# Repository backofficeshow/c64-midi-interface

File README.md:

# c64-midi-interface

A hardware layout to accompany this website what I found while in a stream:

http://little-scale.blogspot.com/2010/03/how-to-make-commodore-64-midi-interface.html

Do please check before having 200 boards made up.

Bye!

xxxx Dr A

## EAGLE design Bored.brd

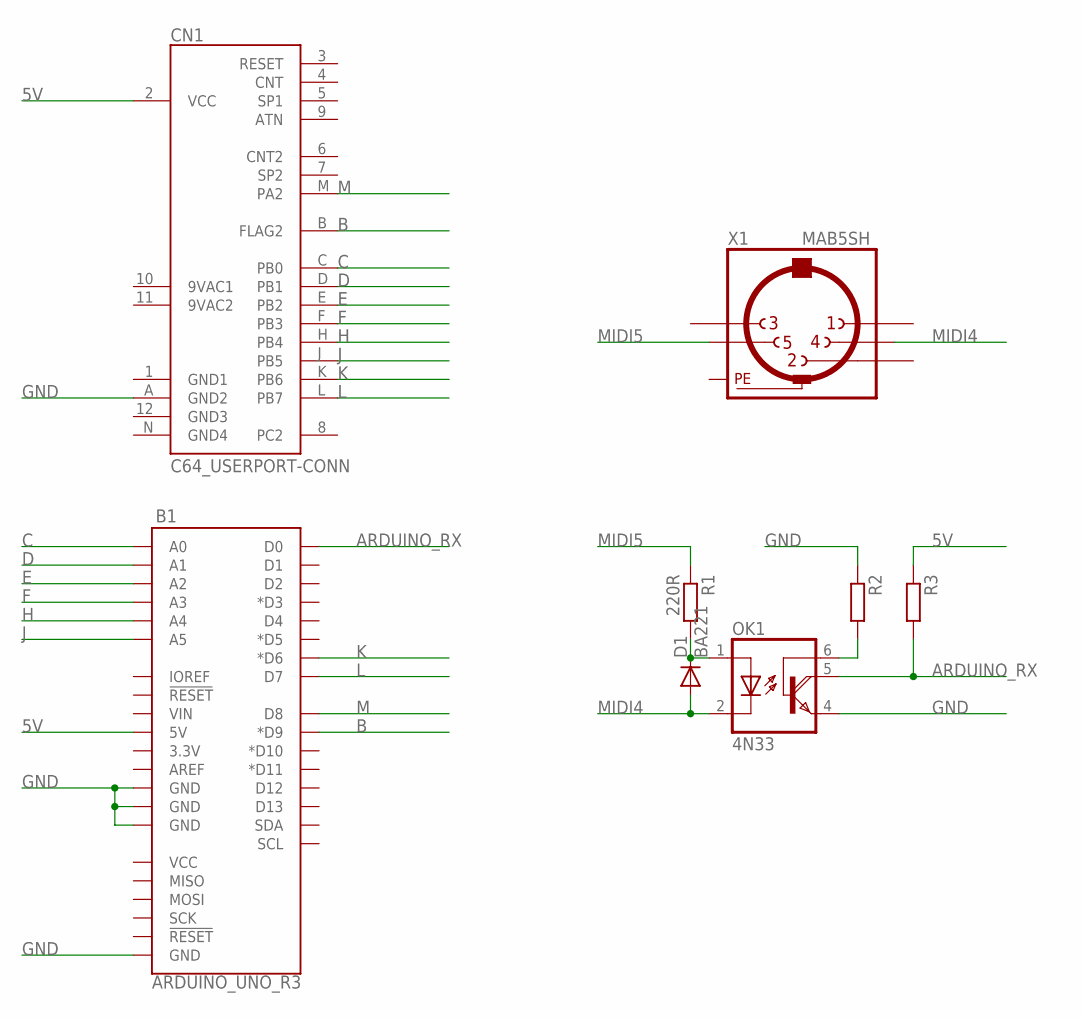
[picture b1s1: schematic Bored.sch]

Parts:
B1: ARDUINO_UNO_R3; ARDUINO_R3
CN1: C64_USERPORT-CONN; UPS24CONN
D1: BA221; DO35-10
OK1: 4N33; DIL06
R1: 220R; 0207/10
R2, R3: R-EU_0207/10; 0207/10
X1: MAB5SH

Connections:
5V: B1.5V, CN1.2 (VCC), R3.1
ARDUINO_RX: B1.D0, OK1.5 (COL), R3.2
B: B1.D9 (*D9), CN1.B (FLAG2)
C: B1.A0, CN1.C (PB0)
D: B1.A1, CN1.D (PB1)
E: B1.A2, CN1.E (PB2)
F: B1.A3, CN1.F (PB3)
GND: B1.GND@1 (GND), B1.GND@2 (GND), B1.GND@3 (GND), B1.GND@4 (GND), CN1.A (GND2), OK1.4 (E), R2.1
H: B1.A4, CN1.H (PB4)
J: B1.A5, CN1.J (PB5)
K: B1.D6 (*D6), CN1.K (PB6)
L: B1.D7, CN1.L (PB7)
M: B1.D8, CN1.M (PA2)
MIDI4: D1.A, OK1.2 (C), X1.4
MIDI5: R1.1, X1.5
unnamed: D1.C, OK1.1 (A), R1.2
unnamed: OK1.6 (B), R2.2
PE: X1.PE, X1.PE@ (PE)

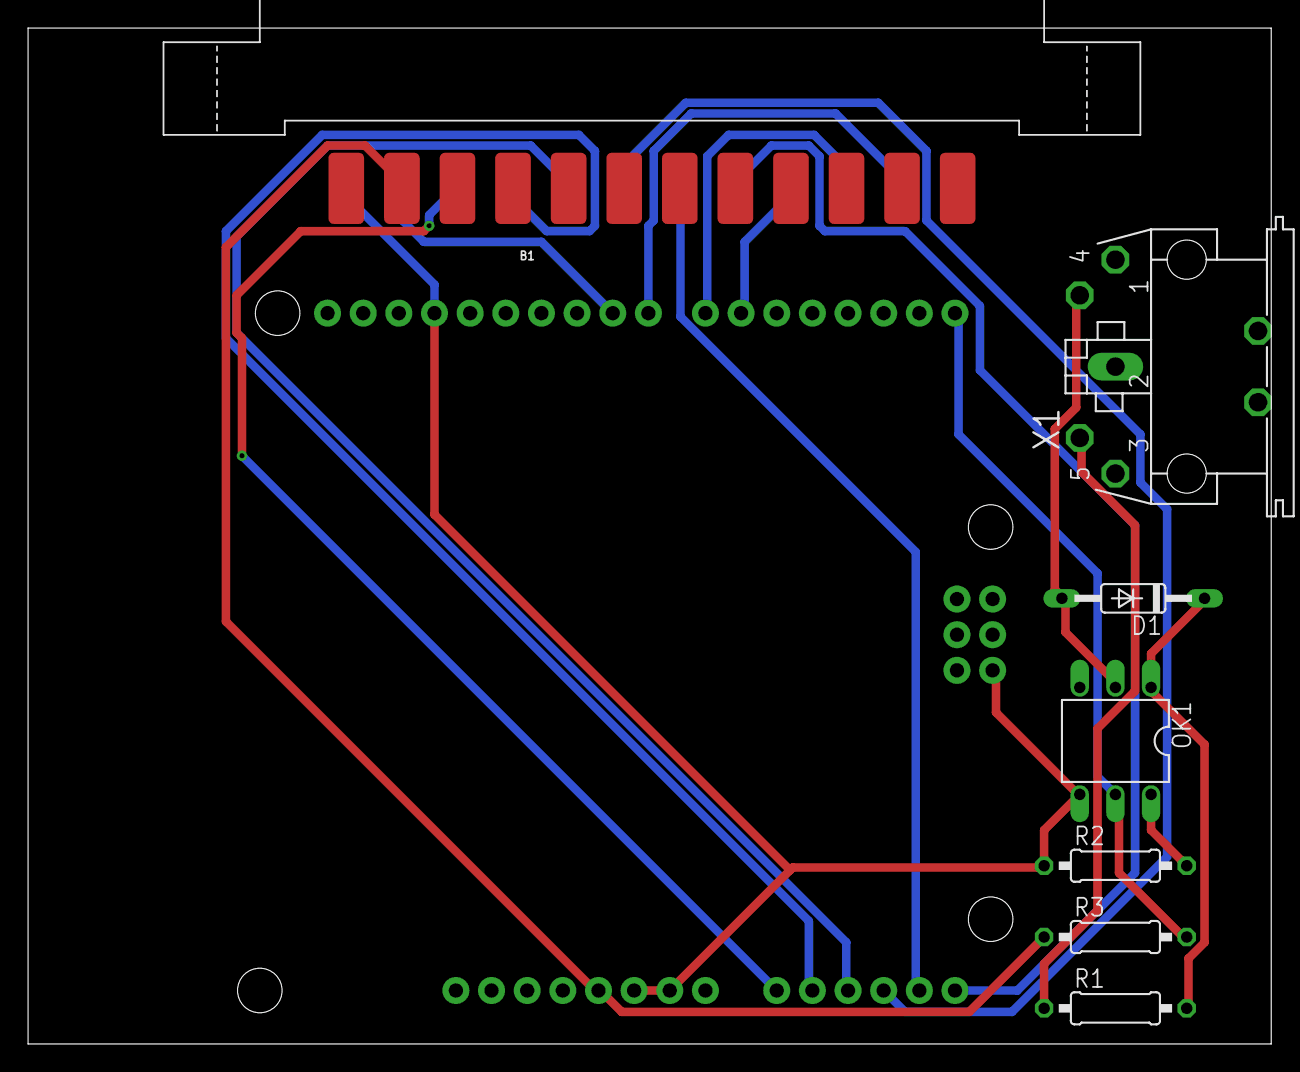
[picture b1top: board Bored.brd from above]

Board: 2 copper layers, 88.6 x 72.4 mm, 8 parts (0 on the bottom side), 18 nets.

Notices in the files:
parts and their libraries:
SparkFun-Boards: Licensing: Creative Commons ShareAlike 4.0 International - https://creativecommons.org/licenses/by-sa/4.0
